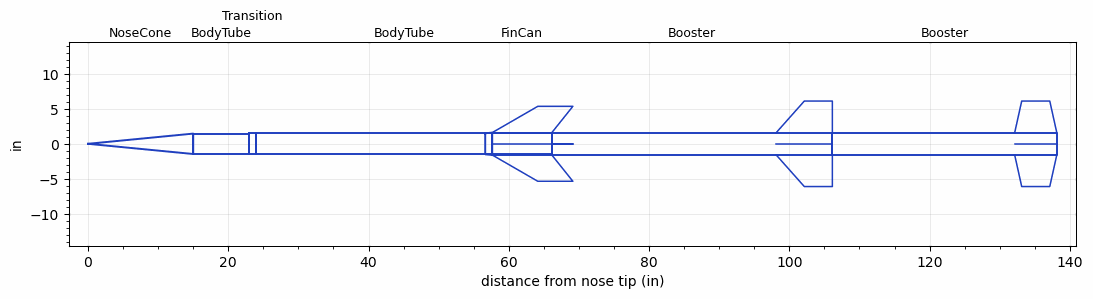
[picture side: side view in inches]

<RASAeroDocument>
 <FileVersion>2</FileVersion>
 <RocketDesign>
  <NoseCone>
   <Length>15</Length>
   <Diameter>2.91</Diameter>
   <Shape>Conical</Shape>
   <BluntRadius>0.065</BluntRadius>
   <Location>0</Location>
  </NoseCone>
  <BodyTube>
   <Length>7.94</Length>
   <Diameter>2.91</Diameter>
   <Location>15</Location>
   <Protuberance>
    <StreamlinedNoBaseDrag>0</StreamlinedNoBaseDrag>
    <StreamlinedWithBaseDrag>0.65</StreamlinedWithBaseDrag>
    <InclinedPlate1Angle>0</InclinedPlate1Angle>
    <InclinedPlate1FrontalArea>0</InclinedPlate1FrontalArea>
    <InclinedPlate2Angle>0</InclinedPlate2Angle>
    <InclinedPlate2FrontalArea>0</InclinedPlate2FrontalArea>
   </Protuberance>
  </BodyTube>
  <Transition>
   <Length>1</Length>
   <Diameter>3</Diameter>
   <Location>22.94</Location>
   <RearDiameter>3</RearDiameter>
  </Transition>
  <BodyTube>
   <Length>42.195</Length>
   <Diameter>3</Diameter>
   <Location>23.94</Location>
  </BodyTube>
  <FinCan>
   <Length>8.5</Length>
   <Diameter>3.19</Diameter>
   <InsideDiameter>3</InsideDiameter>
   <Location>66.135</Location>
   <ShoulderLength>1</ShoulderLength>
   <Offset>-8.5</Offset>
   <Fin>
    <Count>4</Count>
    <Chord>8.5</Chord>
    <Span>3.75</Span>
    <SweepDistance>6.5</SweepDistance>
    <TipChord>5</TipChord>
    <Thickness>0.15</Thickness>
    <LERadius>0.01</LERadius>
    <Location>8.5</Location>
    <AirfoilSection>Hexagonal</AirfoilSection>
    <FX1>0.75</FX1>
    <FX3>0.75</FX3>
   </Fin>
  </FinCan>
  <Booster>
   <Length>40</Length>
   <Diameter>3.19</Diameter>
   <InsideDiameter>3.19</InsideDiameter>
   <LaunchShoeArea>0.4</LaunchShoeArea>
   <Location>66.135</Location>
   <ShoulderLength>0</ShoulderLength>
   <Fin>
    <Count>4</Count>
    <Chord>8</Chord>
    <Span>4.5</Span>
    <SweepDistance>4</SweepDistance>
    <TipChord>4</TipChord>
    <Thickness>0.1875</Thickness>
    <LERadius>0.01</LERadius>
    <Location>8</Location>
    <AirfoilSection>Hexagonal</AirfoilSection>
    <FX1>0.5</FX1>
    <FX3>0.5</FX3>
   </Fin>
  </Booster>
  <Booster>
   <Length>32</Length>
   <Diameter>3.19</Diameter>
   <InsideDiameter>3.19</InsideDiameter>
   <Location>106.135</Location>
   <ShoulderLength>0</ShoulderLength>
   <Fin>
    <Count>4</Count>
    <Chord>6</Chord>
    <Span>4.5</Span>
    <SweepDistance>1</SweepDistance>
    <TipChord>4</TipChord>
    <Thickness>0.133</Thickness>
    <LERadius>0.01</LERadius>
    <Location>6</Location>
    <AirfoilSection>Hexagonal</AirfoilSection>
    <FX1>0.5</FX1>
    <FX3>0.5</FX3>
   </Fin>
  </Booster>
  <Surface>Rough Camouflage Paint</Surface>
  <ModifiedBarrowman>True</ModifiedBarrowman>
  <Turbulence>True</Turbulence>
  <UseBooster1>False</UseBooster1>
  <UseBooster2>False</UseBooster2>
 </RocketDesign>
 <LaunchSite>
  <Altitude>2000</Altitude>
  <Pressure>0</Pressure>
  <RodAngle>1</RodAngle>
  <RodLength>20</RodLength>
  <Temperature>80</Temperature>
  <WindSpeed>5</WindSpeed>
 </LaunchSite>
 <Recovery>
  <Altitude1>1000</Altitude1>
  <Altitude2>1000</Altitude2>
  <DeviceType1>None</DeviceType1>
  <DeviceType2>None</DeviceType2>
  <Event1>False</Event1>
  <Event2>False</Event2>
  <Size1>1</Size1>
  <Size2>1</Size2>
  <EventType1>None</EventType1>
  <EventType2>None</EventType2>
  <CD1>1.33</CD1>
  <CD2>1.33</CD2>
 </Recovery>
 <SimulationList>
  <Simulation>
   <SustainerEngine>N3051  (TsKrush)</SustainerEngine>
   <SustainerLaunchWt>22.67</SustainerLaunchWt>
   <SustainerNozzleDiameter>2.5</SustainerNozzleDiameter>
   <SustainerCG>43</SustainerCG>
   <SustainerIgnitionDelay>8</SustainerIgnitionDelay>
   <Booster1Engine>M2922  (TsKrush)</Booster1Engine>
   <Booster1LaunchWt>37</Booster1LaunchWt>
   <Booster1SeparationDelay>0</Booster1SeparationDelay>
   <Booster1IgnitionDelay>5</Booster1IgnitionDelay>
   <Booster1CG>58.5</Booster1CG>
   <Booster1NozzleDiameter>2.75</Booster1NozzleDiameter>
   <IncludeBooster1>True</IncludeBooster1>
   <Booster2Engine>M2905  (TsKrush)</Booster2Engine>
   <Booster2LaunchWt>50</Booster2LaunchWt>
   <Booster2Delay>0</Booster2Delay>
   <Booster2CG>65</Booster2CG>
   <IncludeBooster2>True</IncludeBooster2>
   <TimetoApogee>136.0785</TimetoApogee>
   <MaxAltitude>248450.6</MaxAltitude>
   <MaxVelocity>5086.305</MaxVelocity>
  </Simulation>
 </SimulationList>
</RASAeroDocument>
